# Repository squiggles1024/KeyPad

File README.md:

# Custom Gaming KeyPad

My second 'finished' prototype of an embedded systems project. This is largely inspired by professional gaming 'keypads' developed by Logitech and Razer. They are essentially a small formfactor keyboard with a button layout that is (supposedly) more ergonomic for gaming. It was programmed on an STM32F4 "Black Pill Board".

This keypad was designed for use with "MMO" style games that require large numbers of easily accessible keys that will map to your character's attacks, abilities, and interface windows (such as the 'pause' menu). In particular, this was designed with World of Warcraft in mind. It features 64 buttons, an LCD capactive touch screen with 12 'touch buttons', and an analog joystick which currently funtions as a mousewheel. The purpose of this project was largely to see how many keybinds I could comfortably fit in the footprint of a typical 'gaming keypad'.

The original design was to use 6 "Mouse Wheels" that could be tilted left, tilted right, pushed in, scrolled up, and scrolled down, which would allow 5 functions in a single hardware device. Ultimately this was scrapped because the 3D Print for the wheels and mechanical parts to make the tilting work were too fragile.

The buttons in the 2nd row from the top are "Navigation switches". These can be tilted in 4 directions and pressed in; thus this single device can function as 5 different buttons. These replaced the mouse wheel idea.
All keys, switches, touch buttons, and joy stick directions (up to 8) can be programmed to function as 1 modifier key (ctrl, shift, alt), a mouse click, mousewheel movement, or a keystroke. As an example, a button can be programmed to be the equivalent of pressing "Mouse Button 3", "Q", "Left Ctrl", and "Mouse Wheel Up" at the same time. It cannot do multiple keystrokes/mouse clicks at one: as in pressing a key cannot be the equivalent of pressing "Q + W", or "Mouse 4 + Mouse 5" simultaneously.

The touchscreen is intended to be used to access the users 'menu interface windows' such as opening their inventory or friends list (buttons that don't need to be pressed often or need to be easily within reach in a pinch). The icons are stored as uchar arrays in RGB888 format in the mcu's flash which is programmed into the lcd screen at startup.

The Black pill board does not have enough GPIO pins to serve all 64 buttons, and the SPI bus for the touch screen, so GPIO expander bonnets were used instead (thank you Adafruit). There are 4 expanders in total, and these are polled using DMA in a round-robin fashion. The touch screen was also a COTS part from Adafruit.

The board design is electrically simple, but mechanically complex. It is effectively a motherboard that interfaces the LCD screen, expander bonnets, and joystick with the microcontroller, the the buttons with the expander bonnets. On the bottom of the board are 4 addressable LEDs (sometimes referred to as "neo pixels).

Known Issue: The LEDs currently do not work. I'm confident that the firmware to make them work in theory is correct, but upon hooking up the PWM signal to a scope, the rise and fall time appear to be too long (The PWM signal looks sinusoidal). Best guess is the wires are too long and there's too much stray capacitance on the PCBA. Also, the cabling ended up taking way more space than anticipated, thus I need to find something to do about the cables because it's currently a mess.

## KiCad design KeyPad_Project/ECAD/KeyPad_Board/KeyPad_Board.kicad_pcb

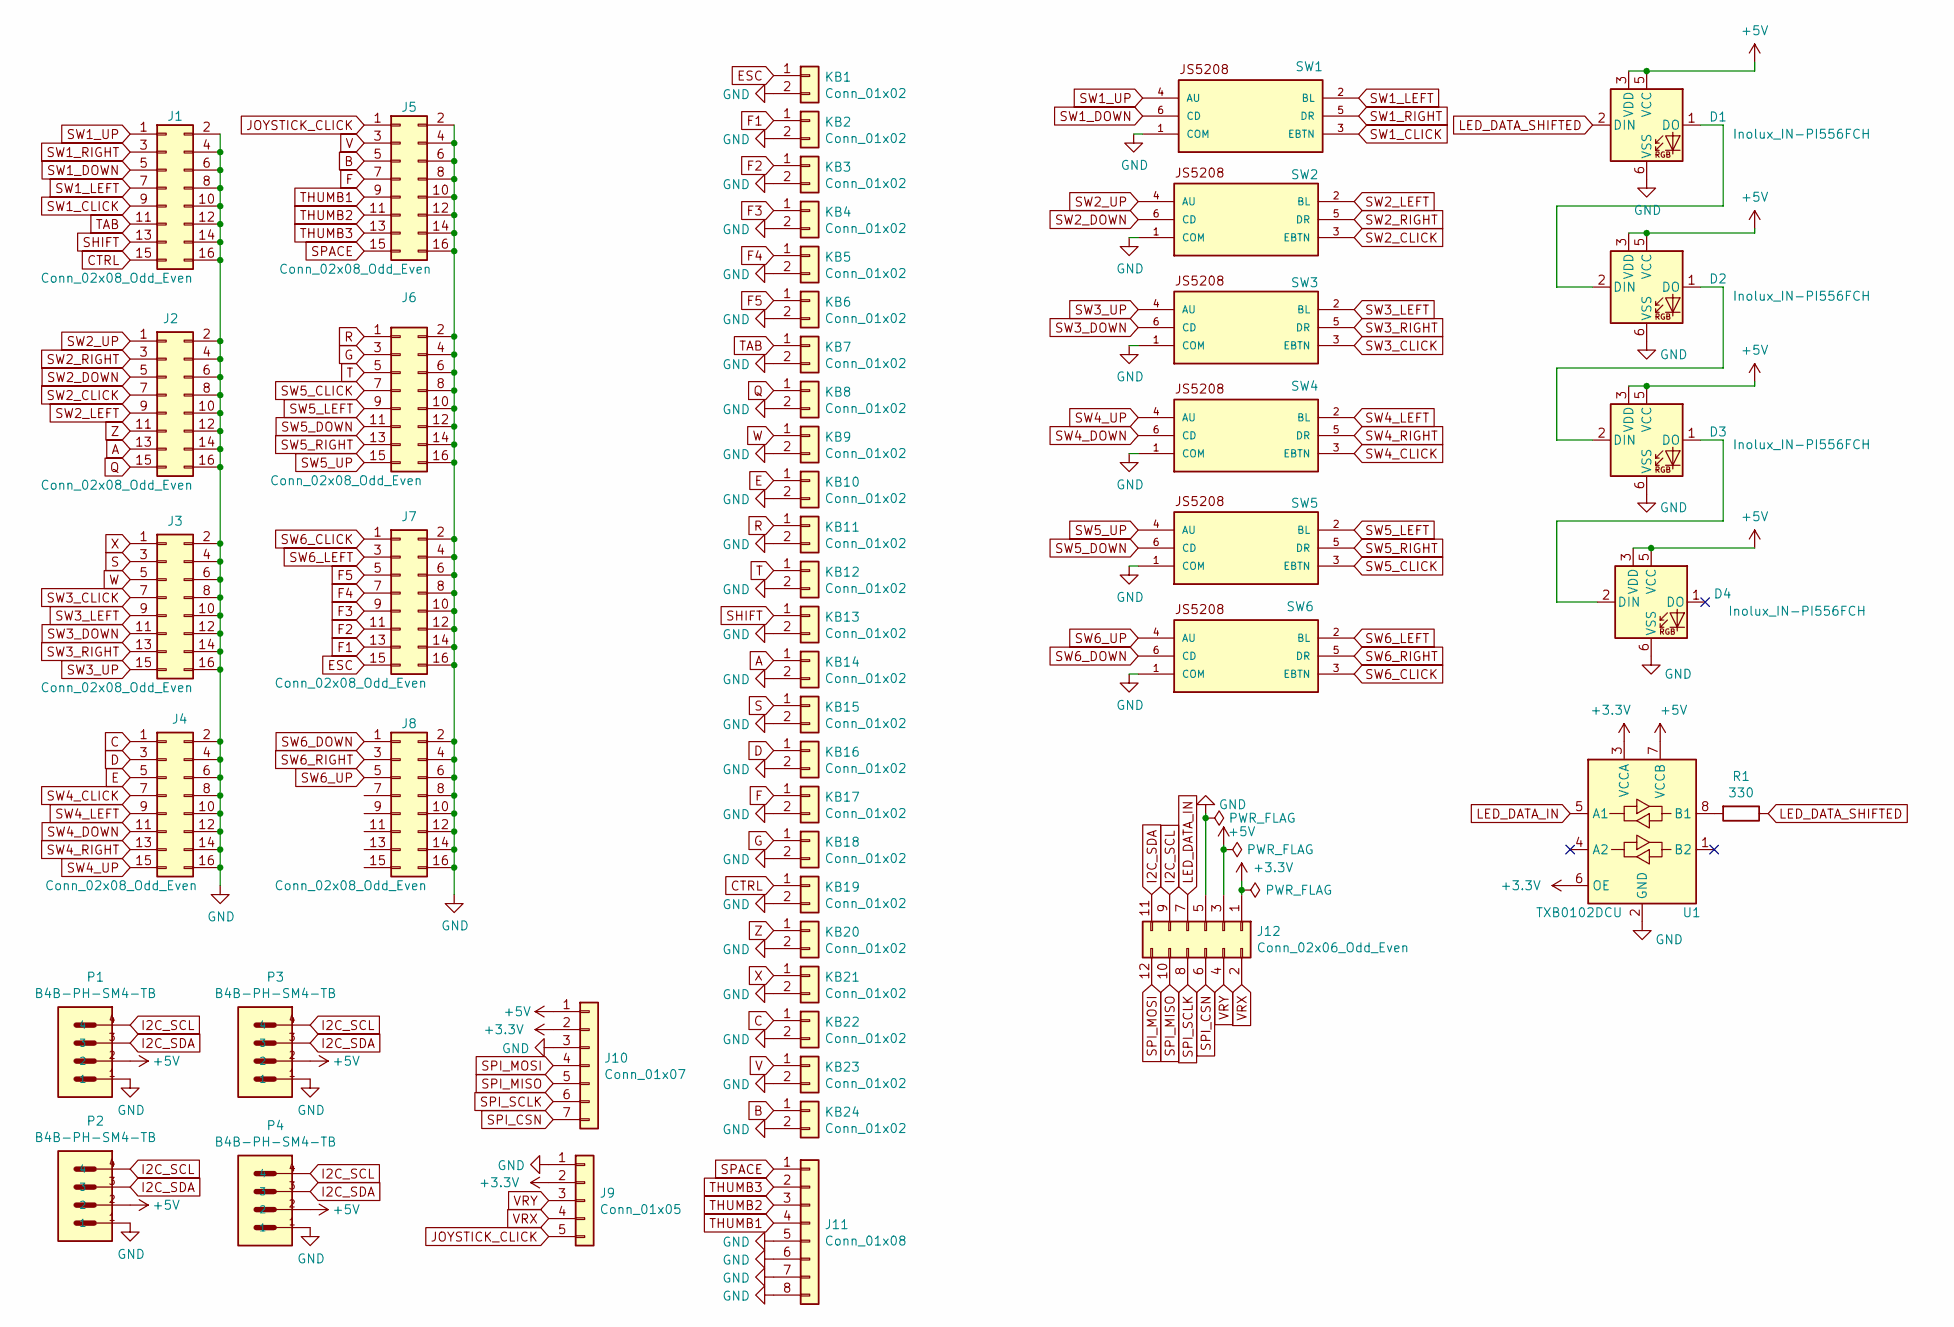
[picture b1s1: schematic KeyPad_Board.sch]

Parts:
D1, D2, D3, D4: Inolux_IN-PI556FCH; LED_WS2812_PLCC6_5.0x5.0mm_P1.6mm
J1, J2, J3, J4, J5, J6, J7, J8: Conn_02x08_Odd_Even; IDC-Header_2x08_P2.54mm_Vertical
J9: Conn_01x05; PinHeader_1x05_P2.54mm_Horizontal
J10: Conn_01x07; PinHeader_1x07_P2.54mm_Vertical
J11: Conn_01x08; PinHeader_1x08_P2.54mm_Vertical
J12: Conn_02x06_Odd_Even; PinHeader_2x06_P2.54mm_Vertical
KB1, KB2, KB3, KB4, KB5, KB6, KB7, KB8, KB9, KB10, KB11, KB12, KB13, KB14, KB15, KB16, KB17, KB18, KB19, KB20, KB21, KB22, KB23, KB24: Conn_01x02; PinHeader_1x02_P2.54mm_Vertical
P1, P2, P3, P4: B4B-PH-SM4-TB; JST_B4B-PH-SM4-TB
R1: 330; R_0603_1608Metric_Pad0.98x0.95mm_HandSolder
SW1, SW2, SW3, SW4, SW5, SW6: JS5208; JS5208_PKG
U1: TXB0102DCU; VSSOP-8_2.4x2.1mm_P0.5mm

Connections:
+3V3: J9.2, J10.2, J12.1, U1.3 (VCCA), U1.6 (OE)
+5V: D1.3 (VDD), D1.5 (VCC), D2.3 (VDD), D2.5 (VCC), D3.3 (VDD), D3.5 (VCC), D4.3 (VDD), D4.5 (VCC), J10.1, J12.3, P1.2, P2.2, P3.2, P4.2, U1.7 (VCCB)
A: J2.13, KB14.1
B: J5.5, KB24.1
C: J4.1, KB22.1
CTRL: J1.15, KB19.1
D: J4.3, KB16.1
E: J4.5, KB10.1
ESC: J7.15, KB1.1
F: J5.7, KB17.1
F1: J7.13, KB2.1
F2: J7.11, KB3.1
F3: J7.9, KB4.1
F4: J7.7, KB5.1
F5: J7.5, KB6.1
G: J6.3, KB18.1
GND: D1.6 (VSS), D2.6 (VSS), D3.6 (VSS), D4.6 (VSS), J1.2, J1.4, J1.6, J1.8, J1.10, J1.12, J1.14, J1.16, J2.2, J2.4, J2.6, J2.8, J2.10, J2.12, J2.14, J2.16, J3.2, J3.4, J3.6, J3.8, J3.10, J3.12, J3.14, J3.16, J4.2, J4.4, J4.6, J4.8, J4.10, J4.12, J4.14, J4.16, J5.2, J5.4, J5.6, J5.8, J5.10, J5.12, J5.14, J5.16, J6.2, J6.4, J6.6, J6.8, J6.10, J6.12, J6.14, J6.16, J7.2, J7.4, J7.6, J7.8, J7.10, J7.12, J7.14, J7.16, J8.2, J8.4, J8.6, J8.8, J8.10, J8.12, J8.14, J8.16, J9.1, J10.3, J11.5, J11.6, J11.7, J11.8, J12.5, KB1.2, KB2.2, KB3.2, KB4.2, KB5.2, KB6.2, KB7.2, KB8.2, KB9.2, KB10.2, KB11.2, KB12.2, KB13.2, KB14.2, KB15.2, KB16.2, KB17.2, KB18.2, KB19.2, KB20.2, KB21.2, KB22.2, KB23.2, KB24.2, P1.1, P2.1, P3.1, P4.1, SW1.1 (COM), SW2.1 (COM), SW3.1 (COM), SW4.1 (COM), SW5.1 (COM), SW6.1 (COM), U1.2 (GND)
I2C_SCL: J12.9, P1.4, P2.4, P3.4, P4.4
I2C_SDA: J12.11, P1.3, P2.3, P3.3, P4.3
JOYSTICK_CLICK: J5.1, J9.5
LED_DATA_IN: J12.7, U1.5 (A1)
LED_DATA_SHIFTED: D1.2 (DIN), R1.1
unnamed: D1.1 (DO), D2.2 (DIN)
unnamed: D2.1 (DO), D3.2 (DIN)
unnamed: D3.1 (DO), D4.2 (DIN)
unnamed: R1.2, U1.8 (B1)
Q: J2.15, KB8.1
R: J6.1, KB11.1
S: J3.3, KB15.1
SHIFT: J1.13, KB13.1
SPACE: J5.15, J11.1
SPI_CSN: J10.7, J12.6
SPI_MISO: J10.5, J12.10
SPI_MOSI: J10.4, J12.12
SPI_SCLK: J10.6, J12.8
SW1_CLICK: J1.9, SW1.3 (EBTN)
SW1_DOWN: J1.5, SW1.6 (CD)
SW1_LEFT: J1.7, SW1.2 (BL)
SW1_RIGHT: J1.3, SW1.5 (DR)
SW1_UP: J1.1, SW1.4 (AU)
SW2_CLICK: J2.7, SW2.3 (EBTN)
SW2_DOWN: J2.5, SW2.6 (CD)
SW2_LEFT: J2.9, SW2.2 (BL)
SW2_RIGHT: J2.3, SW2.5 (DR)
SW2_UP: J2.1, SW2.4 (AU)
SW3_CLICK: J3.7, SW3.3 (EBTN)
SW3_DOWN: J3.11, SW3.6 (CD)
SW3_LEFT: J3.9, SW3.2 (BL)
SW3_RIGHT: J3.13, SW3.5 (DR)
SW3_UP: J3.15, SW3.4 (AU)
SW4_CLICK: J4.7, SW4.3 (EBTN)
SW4_DOWN: J4.11, SW4.6 (CD)
SW4_LEFT: J4.9, SW4.2 (BL)
SW4_RIGHT: J4.13, SW4.5 (DR)
SW4_UP: J4.15, SW4.4 (AU)
SW5_CLICK: J6.7, SW5.3 (EBTN)
SW5_DOWN: J6.11, SW5.6 (CD)
SW5_LEFT: J6.9, SW5.2 (BL)
SW5_RIGHT: J6.13, SW5.5 (DR)
SW5_UP: J6.15, SW5.4 (AU)
SW6_CLICK: J7.1, SW6.3 (EBTN)
SW6_DOWN: J8.1, SW6.6 (CD)
SW6_LEFT: J7.3, SW6.2 (BL)
SW6_RIGHT: J8.3, SW6.5 (DR)
SW6_UP: J8.5, SW6.4 (AU)
T: J6.5, KB12.1
TAB: J1.11, KB7.1
THUMB1: J5.9, J11.4
THUMB2: J5.11, J11.3
THUMB3: J5.13, J11.2
V: J5.3, KB23.1
VRX: J9.4, J12.2
VRY: J9.3, J12.4
W: J3.5, KB9.1
X: J3.1, KB21.1
Z: J2.11, KB20.1

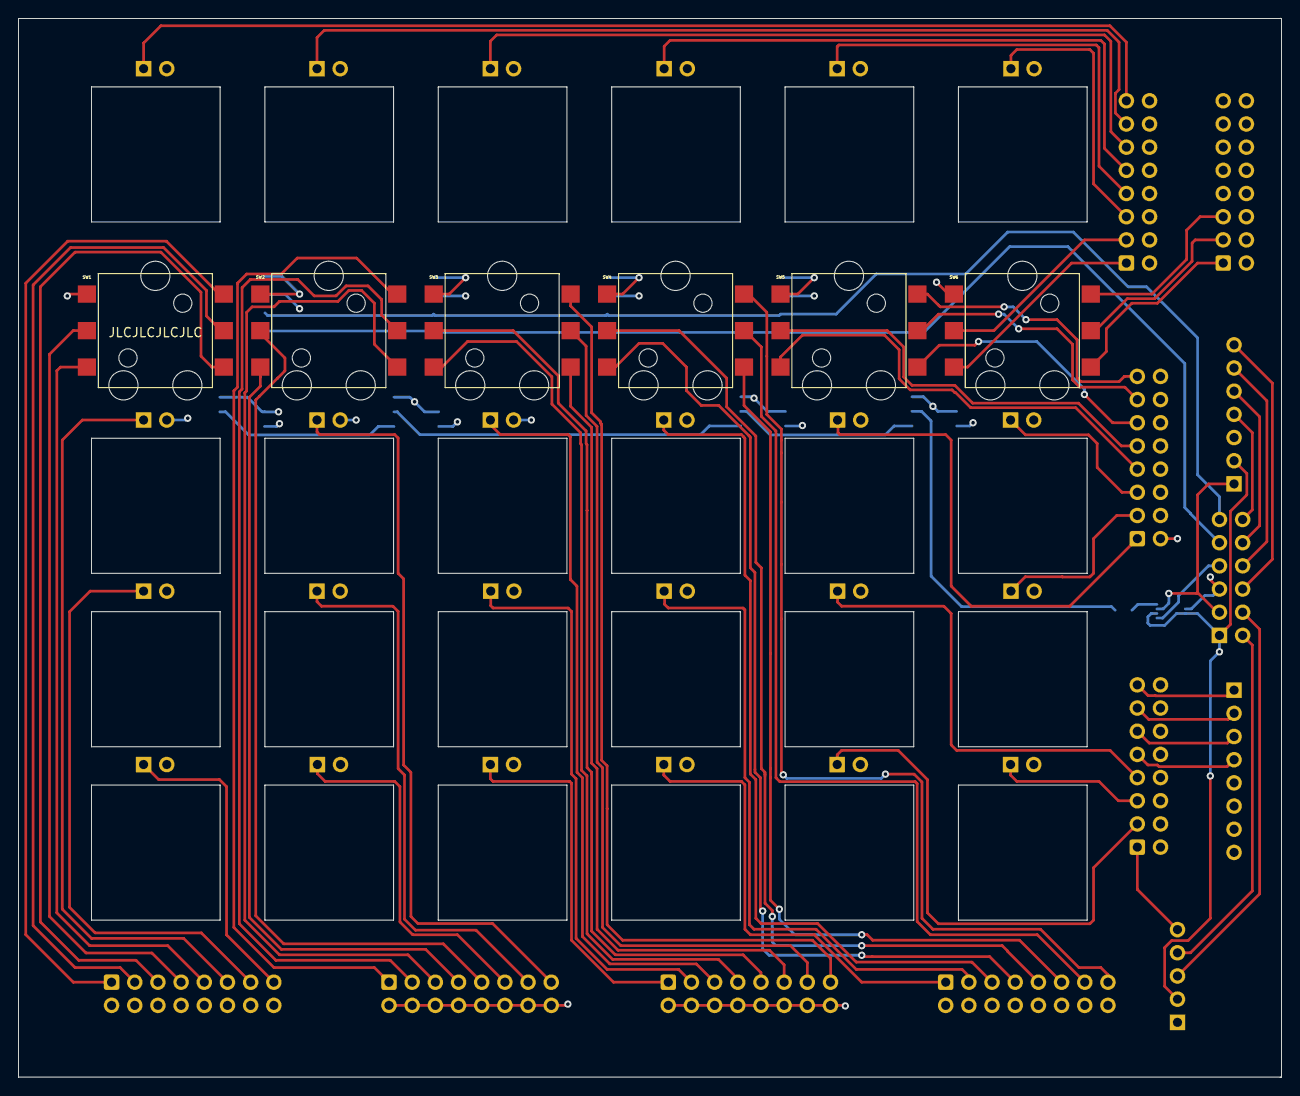
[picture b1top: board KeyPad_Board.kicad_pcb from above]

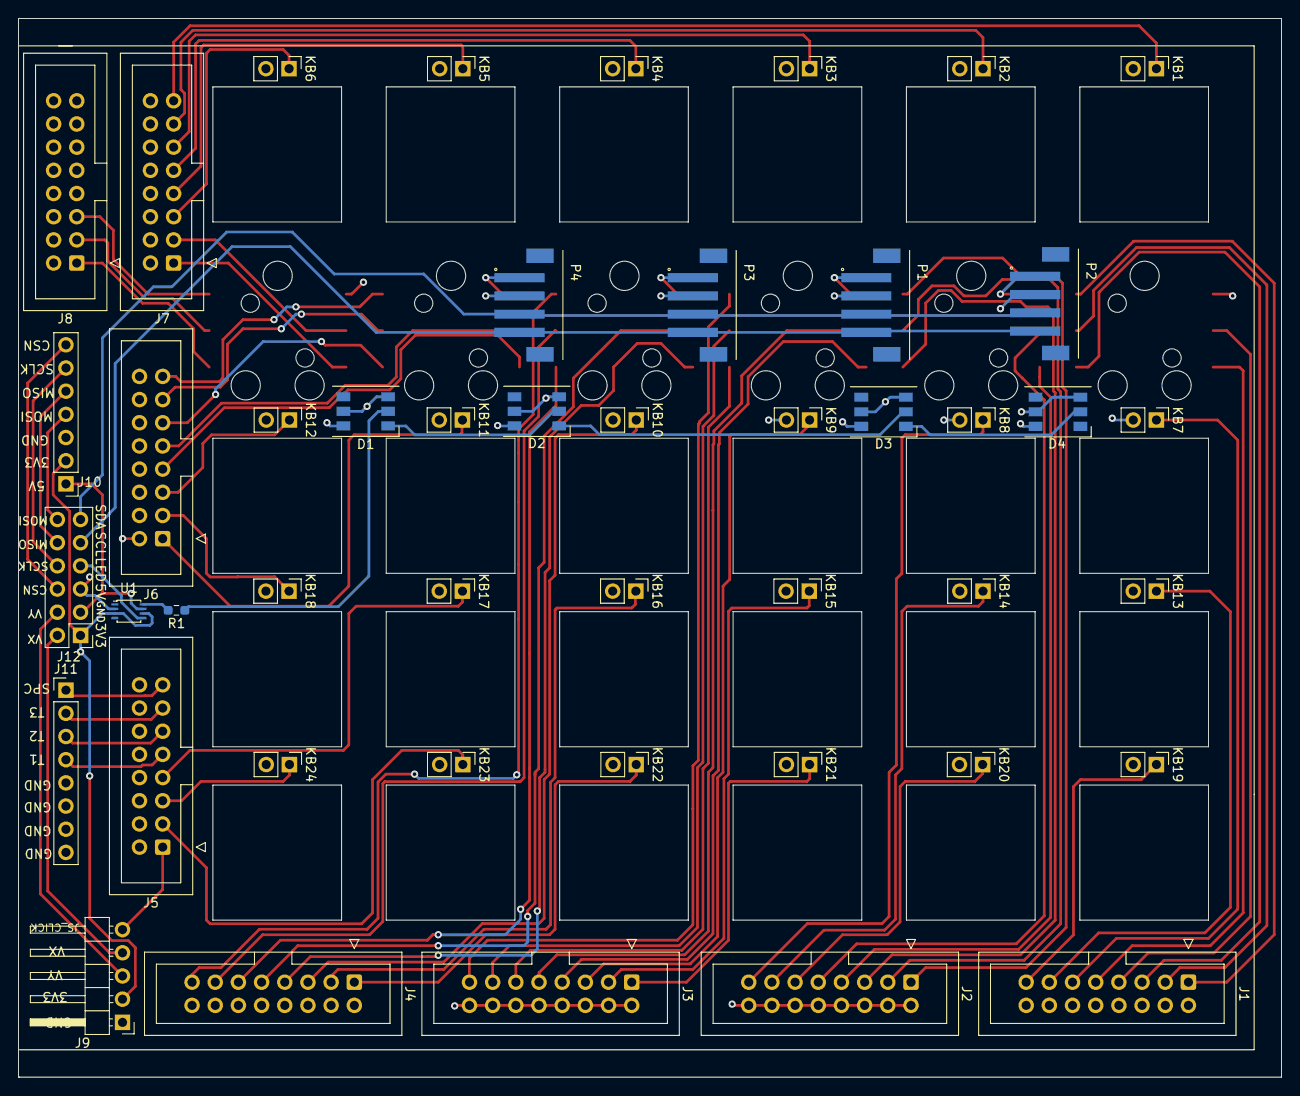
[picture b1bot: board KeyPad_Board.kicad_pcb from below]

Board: 4 copper layers, 138.4 x 116.0 mm, 52 parts (46 on the bottom side), 76 nets.

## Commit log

2022-05-23 Fixed LED timing error
2022-05-23 Added change-mode function
2022-05-24 Fix joystick initialization
2022-05-25 Added ILI9431 Driver
2022-05-25 Added ILI9431 Functions
2022-05-25 Added ILI9431 Headers
2022-05-25 Added icon art assets
2022-05-25 Added screen initilization
2022-05-25 Latest Build
2022-05-28 Added I2C2 Support for TouchScreen
2022-05-28 Added I2C2 Support for Touch Screen
2022-05-28 Added Button IRQ Callback
2022-05-28 Modified ISR to support 2 I2C Handles
2022-05-28 Added experimental Timer init function. Unused.
2022-05-28 Initial Commit of TouchScreen driver
2022-05-28 Made image handle pointer point to const uint8
2022-05-28 initial commit of touch button driver
2022-05-28 Changed Clock prescalar to fix LCD communication
2022-05-28 Changed I2C DMA Init to I2C1 DMA Init
2022-05-28 Added Touch buttons to main
2022-06-24 Adjusted DMA Priorities
2022-06-24 Changed Hardware Initialization Sequencing
2022-06-24 Fixed Comment
2022-06-24 Added Potentiometer offset
2022-06-24 Started Keypad Wrapper/Driver
2022-06-24 Cube IDE Generated code change. Ignore.
2022-06-24 Adjusted IRQ Priority
2022-06-24 Cube IDE Code Change. Ignore
2022-06-24 Added KeyFunction data type
2022-06-24 Adjusted priority of SysTick timebase IRQ.
2022-06-25 Remove Magic Numbers, Datatype Rename
2022-06-25 Added KeyPad Default Keybinds
2022-06-25 Convert to KeyFunction datatype
2022-06-25 Changed Consts to Defines (Fix compiler warning)
2022-06-25 Remove magic numbers, Convert to KeyFunction type
2022-06-25 Replaced KeyPad Part code with KeyPad code
2022-06-25 Finished Init and Tx Buffer functions
2022-06-30 Added comments and headers.
2022-06-30 Added alpha filter for joystick
2022-06-30 Removed CubeIDE Comments
2022-06-30 Added Comments/Headers.
2022-06-30 Fixed Left/Right Joystick Function
2022-07-01 Added ability to change binds
2022-07-01 Added support for multiple interfaces/Endpoints
2022-12-01 Remove magic number
2022-12-01 Add images for readme
2022-12-01 Add CAD Models
